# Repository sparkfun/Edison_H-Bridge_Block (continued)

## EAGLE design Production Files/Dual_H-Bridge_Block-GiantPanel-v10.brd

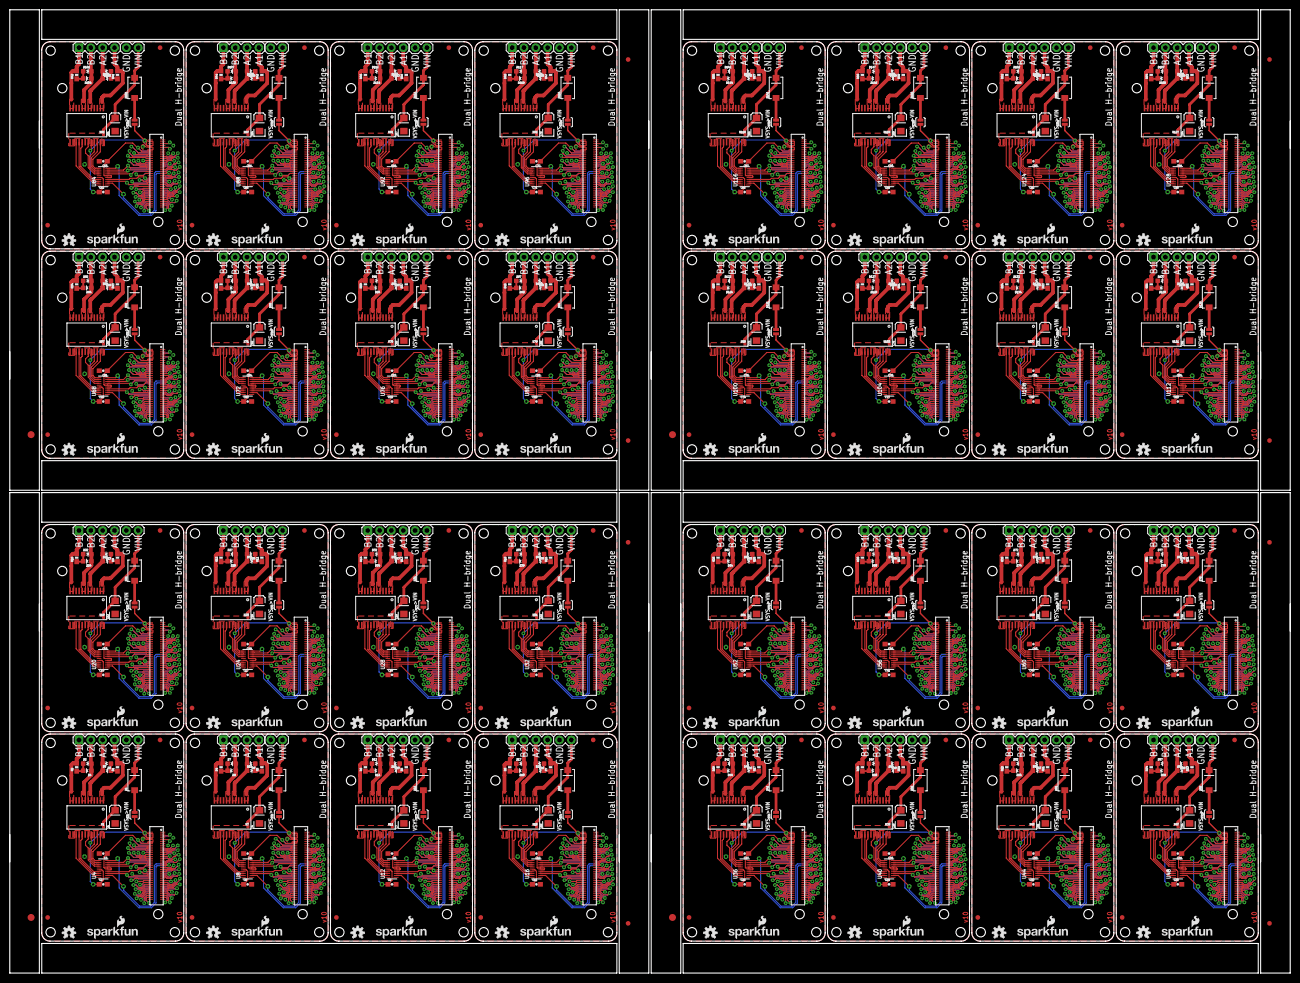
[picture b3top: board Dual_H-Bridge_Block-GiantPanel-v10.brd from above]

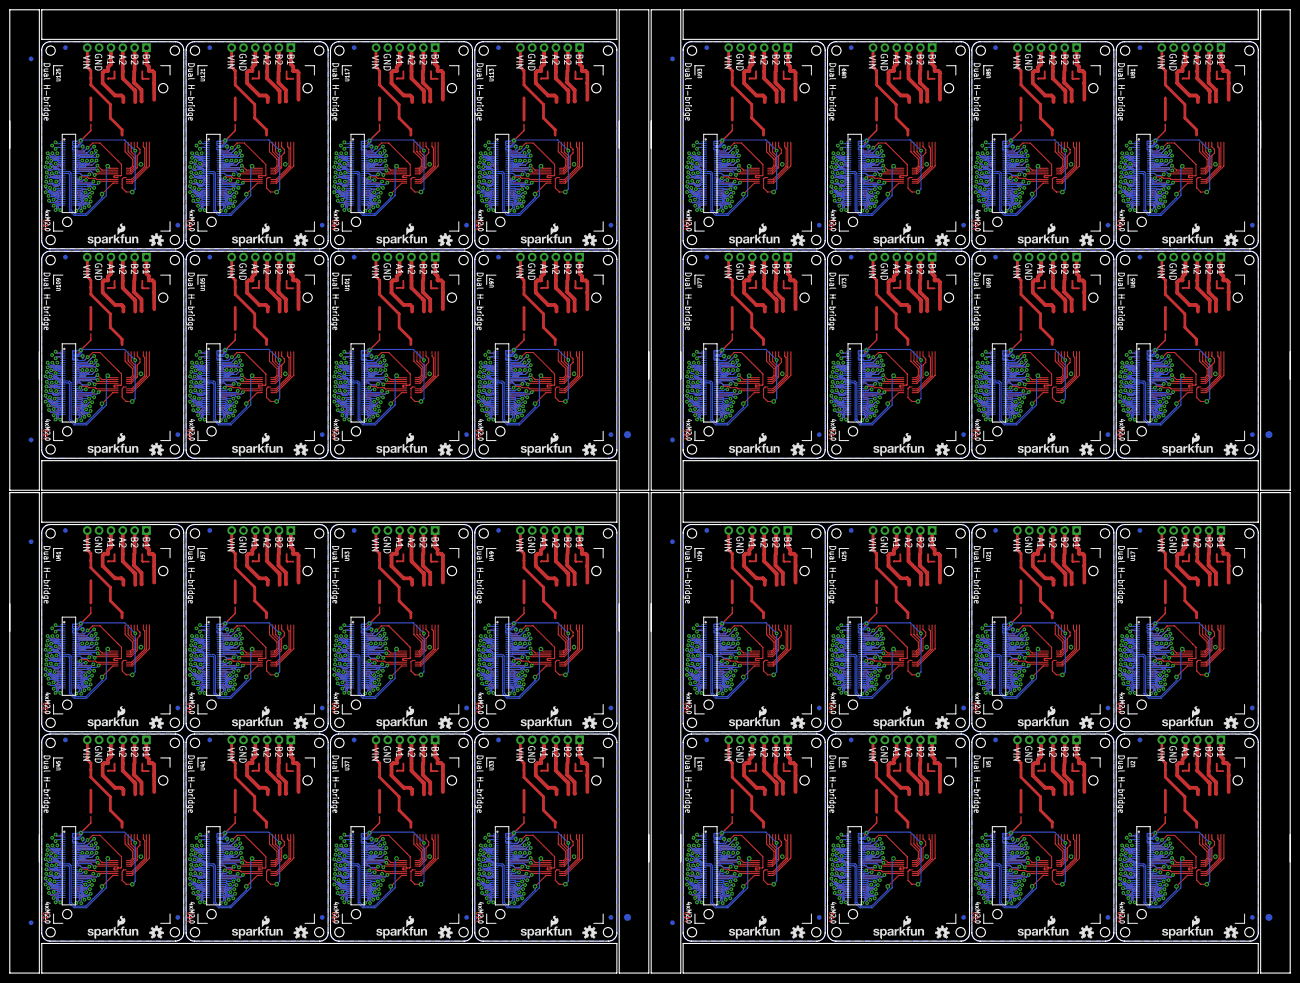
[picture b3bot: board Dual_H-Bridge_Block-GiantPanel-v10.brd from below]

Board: 2 copper layers, 274.8 x 206.8 mm, 824 parts (204 on the bottom side), 2336 nets.

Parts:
C1, C4, C7, C10, C13, C16, C19, C22, C25, C28, C31, C34, C37, C40, C43, C46, C49, C52, C55, C58, C61, C64, C67, C70, C73, C76, C79, C82, C85, C88, C91, C94: 10uF; EIA3216
C2, C3, C5, C6, C8, C9, C11, C12, C14, C15, C17, C18, C20, C21, C23, C24, C26, C27, C29, C30, C32, C33, C35, C36, C38, C39, C41, C42, C44, C45, C47, C48, C50, C51, C53, C54, C56, C57, C59, C60, C62, C63, C65, C66, C68, C69, C71, C72, C74, C75, C77, C78, C80, C81, C83, C84, C86, C87, C89, C90, C92, C93, C95, C96: 0.1uF; 0603-CAP
D1, D6, D11, D16, D21, D26, D31, D36, D41, D46, D51, D56, D61, D66, D71, D76, D81, D86, D91, D96, D101, D106, D111, D116, D121, D126, D131, D136, D141, D146, D151, D156: MBRA140; SMA-DIODE
D2, D3, D7, D8, D12, D13, D17, D18, D22, D23, D27, D28, D32, D33, D37, D38, D42, D43, D47, D48, D52, D53, D57, D58, D62, D63, D67, D68, D72, D73, D77, D78, D82, D83, D87, D88, D92, D93, D97, D98, D102, D103, D107, D108, D112, D113, D117, D118, D122, D123, D127, D128, D132, D133, D137, D138, D142, D143, D147, D148, D152, D153, D157, D158: GREEN; LED-0603
D4, D5, D9, D10, D14, D15, D19, D20, D24, D25, D29, D30, D34, D35, D39, D40, D44, D45, D49, D50, D54, D55, D59, D60, D64, D65, D69, D70, D74, D75, D79, D80, D84, D85, D89, D90, D94, D95, D99, D100, D104, D105, D109, D110, D114, D115, D119, D120, D124, D125, D129, D130, D134, D135, D139, D140, D144, D145, D149, D150, D154, D155, D159, D160: RED; LED-0603
E$1, E$2, E$11, E$12, E$17, E$18, E$23, E$24: FIDUCIAL-1.5X3
E$3, E$4, E$5, E$6, E$7, E$8, E$9, E$10, E$13, E$14, E$15, E$16, E$19, E$20, E$21, E$22: FIDUCIAL-1X2
FID1, FID2, FID3, FID4, FID5, FID6, FID7, FID8, FID9, FID10, FID11, FID12, FID13, FID14, FID15, FID16, FID17, FID18, FID19, FID20, FID21, FID22, FID23, FID24, FID25, FID26, FID27, FID28, FID29, FID30, FID31, FID32, FID33, FID34, FID35, FID36, FID37, FID38, FID39, FID40, FID41, FID42, FID43, FID44, FID45, FID46, FID47, FID48, FID49, FID50, FID51, FID52, FID53, FID54, FID55, FID56, FID57, FID58, FID59, FID60, FID61, FID62, FID63, FID64, FID65, FID66, FID67, FID68, FID69, FID70, FID71, FID72, FID73, FID74, FID75, FID76, FID77, FID78, FID79, FID80, FID81, FID82, FID83, FID84, FID85, FID86, FID87, FID88, FID89, FID90, FID91, FID92, FID93, FID94, FID95, FID96, FID97, FID98, FID99, FID100, FID101, FID102, FID103, FID104, FID105, FID106, FID107, FID108, FID109, FID110, FID111, FID112, FID113, FID114, FID115, FID116, FID117, FID118, FID119, FID120, FID121, FID122, FID123, FID124, FID125, FID126, FID127, FID128: FIDUCIAL1X2; FIDUCIAL-1X2
JP1, JP3, JP5, JP7, JP9, JP11, JP13, JP15, JP17, JP19, JP21, JP23, JP25, JP27, JP29, JP31, JP33, JP35, JP37, JP39, JP41, JP43, JP45, JP47, JP49, JP51, JP53, JP55, JP57, JP59, JP61, JP63: 1X04
JP2, JP4, JP6, JP8, JP10, JP12, JP14, JP16, JP18, JP20, JP22, JP24, JP26, JP28, JP30, JP32, JP34, JP36, JP38, JP40, JP42, JP44, JP46, JP48, JP50, JP52, JP54, JP56, JP58, JP60, JP62, JP64: M02PTH; 1X02
LOGO1, LOGO2, LOGO5, LOGO7, LOGO9, LOGO11, LOGO13, LOGO15, LOGO17, LOGO19, LOGO21, LOGO23, LOGO25, LOGO27, LOGO29, LOGO31, LOGO33, LOGO35, LOGO37, LOGO39, LOGO41, LOGO43, LOGO45, LOGO47, LOGO49, LOGO51, LOGO53, LOGO55, LOGO57, LOGO59, LOGO61, LOGO63, LOGO65, LOGO67, LOGO69, LOGO71, LOGO73, LOGO75, LOGO77, LOGO79, LOGO81, LOGO83, LOGO85, LOGO87, LOGO89, LOGO91, LOGO93, LOGO95, LOGO97, LOGO99, LOGO101, LOGO103, LOGO105, LOGO107, LOGO109, LOGO111, LOGO113, LOGO115, LOGO117, LOGO119, LOGO121, LOGO123, LOGO125, LOGO127: OSHW-LOGOS; OSHW-LOGO-S
LOGO3, LOGO4, LOGO6, LOGO8, LOGO10, LOGO12, LOGO14, LOGO16, LOGO18, LOGO20, LOGO22, LOGO24, LOGO26, LOGO28, LOGO30, LOGO32, LOGO34, LOGO36, LOGO38, LOGO40, LOGO42, LOGO44, LOGO46, LOGO48, LOGO50, LOGO52, LOGO54, LOGO56, LOGO58, LOGO60, LOGO62, LOGO64, LOGO66, LOGO68, LOGO70, LOGO72, LOGO74, LOGO76, LOGO78, LOGO80, LOGO82, LOGO84, LOGO86, LOGO88, LOGO90, LOGO92, LOGO94, LOGO96, LOGO98, LOGO100, LOGO102, LOGO104, LOGO106, LOGO108, LOGO110, LOGO112, LOGO114, LOGO116, LOGO118, LOGO120, LOGO122, LOGO124, LOGO126, LOGO128: SFE_LOGO_NAME_FLAME.1_INCH; SFE_LOGO_NAME_FLAME_.1
R1, R2, R3, R4, R5, R6, R7, R8, R9, R10, R11, R12, R13, R14, R15, R16, R17, R18, R19, R20, R21, R22, R23, R24, R25, R26, R27, R28, R29, R30, R31, R32, R33, R34, R35, R36, R37, R38, R39, R40, R41, R42, R43, R44, R45, R46, R47, R48, R49, R50, R51, R52, R53, R54, R55, R56, R57, R58, R59, R60, R61, R62, R63, R64: 680; 0603-RES
SJ1, SJ2, SJ3, SJ4, SJ5, SJ6, SJ7, SJ8, SJ9, SJ10, SJ11, SJ12, SJ13, SJ14, SJ15, SJ16, SJ17, SJ18, SJ19, SJ20, SJ21, SJ22, SJ23, SJ24, SJ25, SJ26, SJ27, SJ28, SJ29, SJ30, SJ31, SJ32: VSYS ENABLE; PAD-JUMPER-2-NO_YES_SILK
U1, U7, U11, U15, U19, U23, U27, U31, U35, U39, U43, U47, U51, U55, U59, U63, U67, U71, U75, U79, U83, U87, U91, U95, U99, U103, U107, U111, U115, U119, U123, U127: TB6612FNG; SSOP24
U2, U5, U9, U13, U17, U21, U25, U29, U33, U37, U41, U45, U49, U53, U57, U61, U65, U69, U73, U77, U81, U85, U89, U93, U97, U101, U105, U109, U113, U117, U121, U125: EDISON_CONNECTOR_FULLMOUNTING_HOLES; EDISON_DAUGHTER
U3, U6, U10, U14, U18, U22, U26, U30, U34, U38, U42, U46, U50, U54, U58, U62, U66, U70, U74, U78, U82, U86, U90, U94, U98, U102, U106, U110, U114, U118, U122, U126: EDISON_CONNECTOR_FULLHEADER; DF40C-70DP-0.4(51)
U4, U8, U12, U16, U20, U24, U28, U32, U36, U40, U44, U48, U52, U56, U60, U64, U68, U72, U76, U80, U84, U88, U92, U96, U100, U104, U108, U112, U116, U120, U124, U128: TXB0108; UFDFN-20

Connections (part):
1.8V: C3.1, U2.12, U3.12, U4.5, U4.6
1.8V1: C6.1, U5.12, U6.12, U8.5, U8.6
1.8V2: C9.1, U9.12, U10.12, U12.5, U12.6
1.8V3: C12.1, U13.12, U14.12, U16.5, U16.6
1.8V4: C15.1, U17.12, U18.12, U20.5, U20.6
1.8V5: C18.1, U21.12, U22.12, U24.5, U24.6
1.8V6: C21.1, U25.12, U26.12, U28.5, U28.6
1.8V7: C24.1, U29.12, U30.12, U32.5, U32.6
1.8V8: C27.1, U33.12, U34.12, U36.5, U36.6
1.8V9: C30.1, U37.12, U38.12, U40.5, U40.6
1.8V10: C33.1, U41.12, U42.12, U44.5, U44.6
1.8V11: C36.1, U45.12, U46.12, U48.5, U48.6
1.8V12: C39.1, U49.12, U50.12, U52.5, U52.6
1.8V13: C42.1, U53.12, U54.12, U56.5, U56.6
1.8V14: C45.1, U57.12, U58.12, U60.5, U60.6
1.8V15: C48.1, U61.12, U62.12, U64.5, U64.6
1.8V16: C51.1, U65.12, U66.12, U68.5, U68.6
1.8V17: C54.1, U69.12, U70.12, U72.5, U72.6
1.8V18: C57.1, U73.12, U74.12, U76.5, U76.6
1.8V19: C60.1, U77.12, U78.12, U80.5, U80.6
1.8V20: C63.1, U81.12, U82.12, U84.5, U84.6
1.8V21: C66.1, U85.12, U86.12, U88.5, U88.6
1.8V22: C69.1, U89.12, U90.12, U92.5, U92.6
1.8V23: C72.1, U93.12, U94.12, U96.5, U96.6
1.8V24: C75.1, U97.12, U98.12, U100.5, U100.6
1.8V25: C78.1, U101.12, U102.12, U104.5, U104.6
1.8V26: C81.1, U105.12, U106.12, U108.5, U108.6
1.8V27: C84.1, U109.12, U110.12, U112.5, U112.6
1.8V28: C87.1, U113.12, U114.12, U116.5, U116.6
1.8V29: C90.1, U117.12, U118.12, U120.5, U120.6
1.8V30: C93.1, U121.12, U122.12, U124.5, U124.6
1.8V31: C96.1, U125.12, U126.12, U128.5, U128.6
3.3V: U2.8, U2.10, U3.8, U3.10
3.3V1: U5.8, U5.10, U6.8, U6.10
3.3V2: U9.8, U9.10, U10.8, U10.10
3.3V3: U13.8, U13.10, U14.8, U14.10
3.3V4: U17.8, U17.10, U18.8, U18.10
3.3V5: U21.8, U21.10, U22.8, U22.10
3.3V6: U25.8, U25.10, U26.8, U26.10
3.3V7: U29.8, U29.10, U30.8, U30.10
3.3V8: U33.8, U33.10, U34.8, U34.10
3.3V9: U37.8, U37.10, U38.8, U38.10
3.3V10: U41.8, U41.10, U42.8, U42.10
3.3V11: U45.8, U45.10, U46.8, U46.10
3.3V12: U49.8, U49.10, U50.8, U50.10
3.3V13: U53.8, U53.10, U54.8, U54.10
3.3V14: U57.8, U57.10, U58.8, U58.10
3.3V15: U61.8, U61.10, U62.8, U62.10
3.3V16: U65.8, U65.10, U66.8, U66.10
3.3V17: U69.8, U69.10, U70.8, U70.10
3.3V18: U73.8, U73.10, U74.8, U74.10
3.3V19: U77.8, U77.10, U78.8, U78.10
3.3V20: U81.8, U81.10, U82.8, U82.10
3.3V21: U85.8, U85.10, U86.8, U86.10
3.3V22: U89.8, U89.10, U90.8, U90.10
3.3V23: U93.8, U93.10, U94.8, U94.10
3.3V24: U97.8, U97.10, U98.8, U98.10
3.3V25: U101.8, U101.10, U102.8, U102.10
3.3V26: U105.8, U105.10, U106.8, U106.10
3.3V27: U109.8, U109.10, U110.8, U110.10
3.3V28: U113.8, U113.10, U114.8, U114.10
3.3V29: U117.8, U117.10, U118.8, U118.10
3.3V30: U121.8, U121.10, U122.8, U122.10
3.3V31: U125.8, U125.10, U126.8, U126.10
A1: JP1.4, R1.2, U1.1, U1.2
A2: D3.C, D5.A, JP1.3, U1.5, U1.6
A3: D8.C, D10.A, JP3.3, U7.5, U7.6
A4: JP3.4, R3.2, U7.1, U7.2
A5: D13.C, D15.A, JP5.3, U11.5, U11.6
A6: JP5.4, R5.2, U11.1, U11.2
A7: D18.C, D20.A, JP7.3, U15.5, U15.6
A8: JP7.4, R7.2, U15.1, U15.2
A9: D23.C, D25.A, JP9.3, U19.5, U19.6
A10: JP9.4, R9.2, U19.1, U19.2
A11: D28.C, D30.A, JP11.3, U23.5, U23.6
A12: JP11.4, R11.2, U23.1, U23.2
A13: D33.C, D35.A, JP13.3, U27.5, U27.6
A14: JP13.4, R13.2, U27.1, U27.2
A15: D38.C, D40.A, JP15.3, U31.5, U31.6
A16: JP15.4, R15.2, U31.1, U31.2
A17: D43.C, D45.A, JP17.3, U35.5, U35.6
A18: JP17.4, R17.2, U35.1, U35.2
A19: D48.C, D50.A, JP19.3, U39.5, U39.6
A20: JP19.4, R19.2, U39.1, U39.2
A21: D53.C, D55.A, JP21.3, U43.5, U43.6
A22: JP21.4, R21.2, U43.1, U43.2
A23: D58.C, D60.A, JP23.3, U47.5, U47.6
A24: JP23.4, R23.2, U47.1, U47.2
A25: D63.C, D65.A, JP25.3, U51.5, U51.6
A26: JP25.4, R25.2, U51.1, U51.2
A27: D68.C, D70.A, JP27.3, U55.5, U55.6
A28: JP27.4, R27.2, U55.1, U55.2
A29: D73.C, D75.A, JP29.3, U59.5, U59.6
A30: JP29.4, R29.2, U59.1, U59.2
A31: D78.C, D80.A, JP31.3, U63.5, U63.6
A32: JP31.4, R31.2, U63.1, U63.2
A33: D83.C, D85.A, JP33.3, U67.5, U67.6
A34: JP33.4, R33.2, U67.1, U67.2
A35: D88.C, D90.A, JP35.3, U71.5, U71.6
A36: JP35.4, R35.2, U71.1, U71.2
A37: D93.C, D95.A, JP37.3, U75.5, U75.6
A38: JP37.4, R37.2, U75.1, U75.2
A39: D98.C, D100.A, JP39.3, U79.5, U79.6
A40: JP39.4, R39.2, U79.1, U79.2
A41: D103.C, D105.A, JP41.3, U83.5, U83.6
A42: JP41.4, R41.2, U83.1, U83.2
A43: D108.C, D110.A, JP43.3, U87.5, U87.6
A44: JP43.4, R43.2, U87.1, U87.2
A45: D113.C, D115.A, JP45.3, U91.5, U91.6
A46: JP45.4, R45.2, U91.1, U91.2
A47: D118.C, D120.A, JP47.3, U95.5, U95.6
A48: JP47.4, R47.2, U95.1, U95.2
A49: D123.C, D125.A, JP49.3, U99.5, U99.6
A50: JP49.4, R49.2, U99.1, U99.2
A51: D128.C, D130.A, JP51.3, U103.5, U103.6
A52: JP51.4, R51.2, U103.1, U103.2
A53: D133.C, D135.A, JP53.3, U107.5, U107.6
A54: JP53.4, R53.2, U107.1, U107.2
A55: D138.C, D140.A, JP55.3, U111.5, U111.6
A56: JP55.4, R55.2, U111.1, U111.2
A57: D143.C, D145.A, JP57.3, U115.5, U115.6
A58: JP57.4, R57.2, U115.1, U115.2
A59: D148.C, D150.A, JP59.3, U119.5, U119.6
A60: JP59.4, R59.2, U119.1, U119.2
A61: D153.C, D155.A, JP61.3, U123.5, U123.6
A62: JP61.4, R61.2, U123.1, U123.2
A63: D158.C, D160.A, JP63.3, U127.5, U127.6
A64: JP63.4, R63.2, U127.1, U127.2
B1: JP1.1, R2.2, U1.11, U1.12
B2: D2.C, D4.A, JP1.2, U1.7, U1.8
B3: JP3.1, R4.2, U7.11, U7.12
B4: D7.C, D9.A, JP3.2, U7.7, U7.8
B5: JP5.1, R6.2, U11.11, U11.12
B6: D12.C, D14.A, JP5.2, U11.7, U11.8
B7: JP7.1, R8.2, U15.11, U15.12
B8: D17.C, D19.A, JP7.2, U15.7, U15.8
B9: JP9.1, R10.2, U19.11, U19.12
B10: D22.C, D24.A, JP9.2, U19.7, U19.8
B11: JP11.1, R12.2, U23.11, U23.12
B12: D27.C, D29.A, JP11.2, U23.7, U23.8
B13: JP13.1, R14.2, U27.11, U27.12
B14: D32.C, D34.A, JP13.2, U27.7, U27.8
B15: JP15.1, R16.2, U31.11, U31.12
B16: D37.C, D39.A, JP15.2, U31.7, U31.8
B17: JP17.1, R18.2, U35.11, U35.12
B18: D42.C, D44.A, JP17.2, U35.7, U35.8
B19: JP19.1, R20.2, U39.11, U39.12
B20: D47.C, D49.A, JP19.2, U39.7, U39.8
B21: JP21.1, R22.2, U43.11, U43.12
B22: D52.C, D54.A, JP21.2, U43.7, U43.8
B23: JP23.1, R24.2, U47.11, U47.12
B24: D57.C, D59.A, JP23.2, U47.7, U47.8
B25: JP25.1, R26.2, U51.11, U51.12
B26: D62.C, D64.A, JP25.2, U51.7, U51.8
B27: JP27.1, R28.2, U55.11, U55.12
B28: D67.C, D69.A, JP27.2, U55.7, U55.8
B29: JP29.1, R30.2, U59.11, U59.12
B30: D72.C, D74.A, JP29.2, U59.7, U59.8
B31: JP31.1, R32.2, U63.11, U63.12
B32: D77.C, D79.A, JP31.2, U63.7, U63.8
B33: JP33.1, R34.2, U67.11, U67.12
B34: D82.C, D84.A, JP33.2, U67.7, U67.8
B35: JP35.1, R36.2, U71.11, U71.12
B36: D87.C, D89.A, JP35.2, U71.7, U71.8
B37: JP37.1, R38.2, U75.11, U75.12
B38: D92.C, D94.A, JP37.2, U75.7, U75.8
B39: JP39.1, R40.2, U79.11, U79.12
B40: D97.C, D99.A, JP39.2, U79.7, U79.8
B41: JP41.1, R42.2, U83.11, U83.12
B42: D102.C, D104.A, JP41.2, U83.7, U83.8
B43: JP43.1, R44.2, U87.11, U87.12
B44: D107.C, D109.A, JP43.2, U87.7, U87.8
B45: JP45.1, R46.2, U91.11, U91.12
B46: D112.C, D114.A, JP45.2, U91.7, U91.8
B47: JP47.1, R48.2, U95.11, U95.12
B48: D117.C, D119.A, JP47.2, U95.7, U95.8
B49: JP49.1, R50.2, U99.11, U99.12
B50: D122.C, D124.A, JP49.2, U99.7, U99.8
B51: JP51.1, R52.2, U103.11, U103.12
B52: D127.C, D129.A, JP51.2, U103.7, U103.8
B53: JP53.1, R54.2, U107.11, U107.12
B54: D132.C, D134.A, JP53.2, U107.7, U107.8
B55: JP55.1, R56.2, U111.11, U111.12
B56: D137.C, D139.A, JP55.2, U111.7, U111.8
B57: JP57.1, R58.2, U115.11, U115.12
B58: D142.C, D144.A, JP57.2, U115.7, U115.8
B59: JP59.1, R60.2, U119.11, U119.12
B60: D147.C, D149.A, JP59.2, U119.7, U119.8
B61: JP61.1, R62.2, U123.11, U123.12
B62: D152.C, D154.A, JP61.2, U123.7, U123.8
B63: JP63.1, R64.2, U127.11, U127.12
B64: D157.C, D159.A, JP63.2, U127.7, U127.8
DCIN: U2.14, U3.14
DCIN1: U5.14, U6.14
DCIN2: U9.14, U10.14
DCIN3: U13.14, U14.14
DCIN4: U17.14, U18.14
DCIN5: U21.14, U22.14
DCIN6: U25.14, U26.14
DCIN7: U29.14, U30.14
DCIN8: U33.14, U34.14
DCIN9: U37.14, U38.14
DCIN10: U41.14, U42.14
DCIN11: U45.14, U46.14
DCIN12: U49.14, U50.14
DCIN13: U53.14, U54.14
DCIN14: U57.14, U58.14
DCIN15: U61.14, U62.14
DCIN16: U65.14, U66.14
DCIN17: U69.14, U70.14
DCIN18: U73.14, U74.14
DCIN19: U77.14, U78.14
DCIN20: U81.14, U82.14
DCIN21: U85.14, U86.14
DCIN22: U89.14, U90.14
DCIN23: U93.14, U94.14
DCIN24: U97.14, U98.14
DCIN25: U101.14, U102.14
DCIN26: U105.14, U106.14
DCIN27: U109.14, U110.14
DCIN28: U113.14, U114.14
DCIN29: U117.14, U118.14
DCIN30: U121.14, U122.14
DCIN31: U125.14, U126.14
FAULT: U2.19, U3.19
FAULT1: U5.19, U6.19
FAULT2: U9.19, U10.19
FAULT3: U13.19, U14.19
FAULT4: U17.19, U18.19
FAULT5: U21.19, U22.19
FAULT6: U25.19, U26.19
FAULT7: U29.19, U30.19
FAULT8: U33.19, U34.19
FAULT9: U37.19, U38.19
FAULT10: U41.19, U42.19
FAULT11: U45.19, U46.19
FAULT12: U49.19, U50.19
FAULT13: U53.19, U54.19
FAULT14: U57.19, U58.19
FAULT15: U61.19, U62.19
FAULT16: U65.19, U66.19
FAULT17: U69.19, U70.19
FAULT18: U73.19, U74.19
FAULT19: U77.19, U78.19
FAULT20: U81.19, U82.19
FAULT21: U85.19, U86.19
FAULT22: U89.19, U90.19
FAULT23: U93.19, U94.19
FAULT24: U97.19, U98.19
FAULT25: U101.19, U102.19
FAULT26: U105.19, U106.19
FAULT27: U109.19, U110.19
FAULT28: U113.19, U114.19
FAULT29: U117.19, U118.19
FAULT30: U121.19, U122.19
FAULT31: U125.19, U126.19
FW_RCVR: U2.69, U3.69
FW_RCVR1: U5.69, U6.69
FW_RCVR2: U9.69, U10.69
FW_RCVR3: U13.69, U14.69
FW_RCVR4: U17.69, U18.69
FW_RCVR5: U21.69, U22.69
FW_RCVR6: U25.69, U26.69
FW_RCVR7: U29.69, U30.69
FW_RCVR8: U33.69, U34.69
FW_RCVR9: U37.69, U38.69
FW_RCVR10: U41.69, U42.69
FW_RCVR11: U45.69, U46.69
FW_RCVR12: U49.69, U50.69
FW_RCVR13: U53.69, U54.69
FW_RCVR14: U57.69, U58.69
FW_RCVR15: U61.69, U62.69
FW_RCVR16: U65.69, U66.69
FW_RCVR17: U69.69, U70.69
FW_RCVR18: U73.69, U74.69
FW_RCVR19: U77.69, U78.69
FW_RCVR20: U81.69, U82.69
FW_RCVR21: U85.69, U86.69
FW_RCVR22: U89.69, U90.69
FW_RCVR23: U93.69, U94.69
FW_RCVR24: U97.69, U98.69
FW_RCVR25: U101.69, U102.69
FW_RCVR26: U105.69, U106.69
FW_RCVR27: U109.69, U110.69
FW_RCVR28: U113.69, U114.69
FW_RCVR29: U117.69, U118.69
FW_RCVR30: U121.69, U122.69
FW_RCVR31: U125.69, U126.69
GND: C1.C, C2.2, C3.2, JP2.1, U1.3, U1.4, U1.9, U1.10, U1.18, U2.1, U2.5, U2.9, U2.11, U2.13, U2.15, U3.1, U3.5, U3.9, U3.11, U3.13, U3.15, U4.15
GND1: C4.C, C5.2, C6.2, JP4.1, U5.1, U5.5, U5.9, U5.11, U5.13, U5.15, U6.1, U6.5, U6.9, U6.11, U6.13, U6.15, U7.3, U7.4, U7.9, U7.10, U7.18, U8.15
GND2: C7.C, C8.2, C9.2, JP6.1, U9.1, U9.5, U9.9, U9.11, U9.13, U9.15, U10.1, U10.5, U10.9, U10.11, U10.13, U10.15, U11.3, U11.4, U11.9, U11.10, U11.18, U12.15
GND3: C10.C, C11.2, C12.2, JP8.1, U13.1, U13.5, U13.9, U13.11, U13.13, U13.15, U14.1, U14.5, U14.9, U14.11, U14.13, U14.15, U15.3, U15.4, U15.9, U15.10, U15.18, U16.15
GND4: C13.C, C14.2, C15.2, JP10.1, U17.1, U17.5, U17.9, U17.11, U17.13, U17.15, U18.1, U18.5, U18.9, U18.11, U18.13, U18.15, U19.3, U19.4, U19.9, U19.10, U19.18, U20.15
GND5: C16.C, C17.2, C18.2, JP12.1, U21.1, U21.5, U21.9, U21.11, U21.13, U21.15, U22.1, U22.5, U22.9, U22.11, U22.13, U22.15, U23.3, U23.4, U23.9, U23.10, U23.18, U24.15
GND6: C19.C, C20.2, C21.2, JP14.1, U25.1, U25.5, U25.9, U25.11, U25.13, U25.15, U26.1, U26.5, U26.9, U26.11, U26.13, U26.15, U27.3, U27.4, U27.9, U27.10, U27.18, U28.15
GND7: C22.C, C23.2, C24.2, JP16.1, U29.1, U29.5, U29.9, U29.11, U29.13, U29.15, U30.1, U30.5, U30.9, U30.11, U30.13, U30.15, U31.3, U31.4, U31.9, U31.10, U31.18, U32.15
GND8: C25.C, C26.2, C27.2, JP18.1, U33.1, U33.5, U33.9, U33.11, U33.13, U33.15, U34.1, U34.5, U34.9, U34.11, U34.13, U34.15, U35.3, U35.4, U35.9, U35.10, U35.18, U36.15
GND9: C28.C, C29.2, C30.2, JP20.1, U37.1, U37.5, U37.9, U37.11, U37.13, U37.15, U38.1, U38.5, U38.9, U38.11, U38.13, U38.15, U39.3, U39.4, U39.9, U39.10, U39.18, U40.15
GND10: C31.C, C32.2, C33.2, JP22.1, U41.1, U41.5, U41.9, U41.11, U41.13, U41.15, U42.1, U42.5, U42.9, U42.11, U42.13, U42.15, U43.3, U43.4, U43.9, U43.10, U43.18, U44.15
GND11: C34.C, C35.2, C36.2, JP24.1, U45.1, U45.5, U45.9, U45.11, U45.13, U45.15, U46.1, U46.5, U46.9, U46.11, U46.13, U46.15, U47.3, U47.4, U47.9, U47.10, U47.18, U48.15
GND12: C37.C, C38.2, C39.2, JP26.1, U49.1, U49.5, U49.9, U49.11, U49.13, U49.15, U50.1, U50.5, U50.9, U50.11, U50.13, U50.15, U51.3, U51.4, U51.9, U51.10, U51.18, U52.15
GND13: C40.C, C41.2, C42.2, JP28.1, U53.1, U53.5, U53.9, U53.11, U53.13, U53.15, U54.1, U54.5, U54.9, U54.11, U54.13, U54.15, U55.3, U55.4, U55.9, U55.10, U55.18, U56.15
GND14: C43.C, C44.2, C45.2, JP30.1, U57.1, U57.5, U57.9, U57.11, U57.13, U57.15, U58.1, U58.5, U58.9, U58.11, U58.13, U58.15, U59.3, U59.4, U59.9, U59.10, U59.18, U60.15
GND15: C46.C, C47.2, C48.2, JP32.1, U61.1, U61.5, U61.9, U61.11, U61.13, U61.15, U62.1, U62.5, U62.9, U62.11, U62.13, U62.15, U63.3, U63.4, U63.9, U63.10, U63.18, U64.15
GND16: C49.C, C50.2, C51.2, JP34.1, U65.1, U65.5, U65.9, U65.11, U65.13, U65.15, U66.1, U66.5, U66.9, U66.11, U66.13, U66.15, U67.3, U67.4, U67.9, U67.10, U67.18, U68.15
GND17: C52.C, C53.2, C54.2, JP36.1, U69.1, U69.5, U69.9, U69.11, U69.13, U69.15, U70.1, U70.5, U70.9, U70.11, U70.13, U70.15, U71.3, U71.4, U71.9, U71.10, U71.18, U72.15
GND18: C55.C, C56.2, C57.2, JP38.1, U73.1, U73.5, U73.9, U73.11, U73.13, U73.15, U74.1, U74.5, U74.9, U74.11, U74.13, U74.15, U75.3, U75.4, U75.9, U75.10, U75.18, U76.15
GND19: C58.C, C59.2, C60.2, JP40.1, U77.1, U77.5, U77.9, U77.11, U77.13, U77.15, U78.1, U78.5, U78.9, U78.11, U78.13, U78.15, U79.3, U79.4, U79.9, U79.10, U79.18, U80.15
GND20: C61.C, C62.2, C63.2, JP42.1, U81.1, U81.5, U81.9, U81.11, U81.13, U81.15, U82.1, U82.5, U82.9, U82.11, U82.13, U82.15, U83.3, U83.4, U83.9, U83.10, U83.18, U84.15
GND21: C64.C, C65.2, C66.2, JP44.1, U85.1, U85.5, U85.9, U85.11, U85.13, U85.15, U86.1, U86.5, U86.9, U86.11, U86.13, U86.15, U87.3, U87.4, U87.9, U87.10, U87.18, U88.15
GND22: C67.C, C68.2, C69.2, JP46.1, U89.1, U89.5, U89.9, U89.11, U89.13, U89.15, U90.1, U90.5, U90.9, U90.11, U90.13, U90.15, U91.3, U91.4, U91.9, U91.10, U91.18, U92.15
GND23: C70.C, C71.2, C72.2, JP48.1, U93.1, U93.5, U93.9, U93.11, U93.13, U93.15, U94.1, U94.5, U94.9, U94.11, U94.13, U94.15, U95.3, U95.4, U95.9, U95.10, U95.18, U96.15
GND24: C73.C, C74.2, C75.2, JP50.1, U97.1, U97.5, U97.9, U97.11, U97.13, U97.15, U98.1, U98.5, U98.9, U98.11, U98.13, U98.15, U99.3, U99.4, U99.9, U99.10, U99.18, U100.15
GND25: C76.C, C77.2, C78.2, JP52.1, U101.1, U101.5, U101.9, U101.11, U101.13, U101.15, U102.1, U102.5, U102.9, U102.11, U102.13, U102.15, U103.3, U103.4, U103.9, U103.10, U103.18, U104.15
GND26: C79.C, C80.2, C81.2, JP54.1, U105.1, U105.5, U105.9, U105.11, U105.13, U105.15, U106.1, U106.5, U106.9, U106.11, U106.13, U106.15, U107.3, U107.4, U107.9, U107.10, U107.18, U108.15
GND27: C82.C, C83.2, C84.2, JP56.1, U109.1, U109.5, U109.9, U109.11, U109.13, U109.15, U110.1, U110.5, U110.9, U110.11, U110.13, U110.15, U111.3, U111.4, U111.9, U111.10, U111.18, U112.15
GND28: C85.C, C86.2, C87.2, JP58.1, U113.1, U113.5, U113.9, U113.11, U113.13, U113.15, U114.1, U114.5, U114.9, U114.11, U114.13, U114.15, U115.3, U115.4, U115.9, U115.10, U115.18, U116.15
GND29: C88.C, C89.2, C90.2, JP60.1, U117.1, U117.5, U117.9, U117.11, U117.13, U117.15, U118.1, U118.5, U118.9, U118.11, U118.13, U118.15, U119.3, U119.4, U119.9, U119.10, U119.18, U120.15
GND30: C91.C, C92.2, C93.2, JP62.1, U121.1, U121.5, U121.9, U121.11, U121.13, U121.15, U122.1, U122.5, U122.9, U122.11, U122.13, U122.15, U123.3, U123.4, U123.9, U123.10, U123.18, U124.15
GND31: C94.C, C95.2, C96.2, JP64.1, U125.1, U125.5, U125.9, U125.11, U125.13, U125.15, U126.1, U126.5, U126.9, U126.11, U126.13, U126.15, U127.3, U127.4, U127.9, U127.10, U127.18, U128.15
GP1: U5.48, U6.48, U8.3
GP2: U5.42, U6.42, U8.4
GP3: U5.34, U6.34, U8.7
GP4: U5.32, U6.32, U8.8
GP5: U5.30, U6.30, U8.9
GP6: U5.28, U6.28
GP7: U5.26, U6.26
GP8: U5.25, U6.25
GP9: U5.24, U6.24
GP10: U9.48, U10.48, U12.3
GP11: U9.42, U10.42, U12.4
GP12: U9.34, U10.34, U12.7
GP12_PWM0: U2.35, U3.35, U4.10
GP12_PWM1: U5.35, U6.35, U8.10
GP12_PWM2: U9.35, U10.35, U12.10
GP12_PWM3: U13.35, U14.35, U16.10
GP12_PWM4: U17.35, U18.35, U20.10
GP12_PWM5: U21.35, U22.35, U24.10
GP12_PWM6: U25.35, U26.35, U28.10
GP12_PWM7: U29.35, U30.35, U32.10
GP12_PWM8: U33.35, U34.35, U36.10
GP12_PWM9: U37.35, U38.35, U40.10
GP12_PWM10: U41.35, U42.35, U44.10
GP12_PWM11: U45.35, U46.35, U48.10
GP12_PWM12: U49.35, U50.35, U52.10
GP12_PWM13: U53.35, U54.35, U56.10
GP12_PWM14: U57.35, U58.35, U60.10
GP12_PWM15: U61.35, U62.35, U64.10
GP12_PWM16: U65.35, U66.35, U68.10
GP12_PWM17: U69.35, U70.35, U72.10
GP12_PWM18: U73.35, U74.35, U76.10
GP12_PWM19: U77.35, U78.35, U80.10
GP12_PWM20: U81.35, U82.35, U84.10
GP12_PWM21: U85.35, U86.35, U88.10
GP12_PWM22: U89.35, U90.35, U92.10
GP12_PWM23: U93.35, U94.35, U96.10
GP12_PWM24: U97.35, U98.35, U100.10
GP12_PWM25: U101.35, U102.35, U104.10
GP12_PWM26: U105.35, U106.35, U108.10
GP12_PWM27: U109.35, U110.35, U112.10
GP12_PWM28: U113.35, U114.35, U116.10
GP12_PWM29: U117.35, U118.35, U120.10
GP12_PWM30: U121.35, U122.35, U124.10
GP12_PWM31: U125.35, U126.35, U128.10
GP13: U9.32, U10.32, U12.8
GP13_PWM1: U2.33, U3.33, U4.2
GP13_PWM2: U5.33, U6.33, U8.2
GP13_PWM3: U9.33, U10.33, U12.2
GP13_PWM4: U13.33, U14.33, U16.2
GP13_PWM5: U17.33, U18.33, U20.2
GP13_PWM6: U21.33, U22.33, U24.2
GP13_PWM7: U25.33, U26.33, U28.2
GP13_PWM8: U29.33, U30.33, U32.2
GP13_PWM9: U33.33, U34.33, U36.2
GP13_PWM10: U37.33, U38.33, U40.2
GP13_PWM11: U41.33, U42.33, U44.2
GP13_PWM12: U45.33, U46.33, U48.2
GP13_PWM13: U49.33, U50.33, U52.2
GP13_PWM14: U53.33, U54.33, U56.2
GP13_PWM15: U57.33, U58.33, U60.2
GP13_PWM16: U61.33, U62.33, U64.2
GP13_PWM17: U65.33, U66.33, U68.2
GP13_PWM18: U69.33, U70.33, U72.2
GP13_PWM19: U73.33, U74.33, U76.2
GP13_PWM20: U77.33, U78.33, U80.2
GP13_PWM21: U81.33, U82.33, U84.2
GP13_PWM22: U85.33, U86.33, U88.2
GP13_PWM23: U89.33, U90.33, U92.2
GP13_PWM24: U93.33, U94.33, U96.2
GP13_PWM25: U97.33, U98.33, U100.2
GP13_PWM26: U101.33, U102.33, U104.2
GP13_PWM27: U105.33, U106.33, U108.2
GP13_PWM28: U109.33, U110.33, U112.2
GP13_PWM29: U113.33, U114.33, U116.2
GP13_PWM30: U117.33, U118.33, U120.2
GP13_PWM31: U121.33, U122.33, U124.2
GP13_PWM32: U125.33, U126.33, U128.2
GP14: U2.48, U3.48, U4.3
GP15: U2.42, U3.42, U4.4
GP16: U9.30, U10.30, U12.9
GP17: U9.28, U10.28
GP18: U9.26, U10.26
GP19: U9.25, U10.25
GP19_I2C_1_SCL: U2.41, U3.41
GP19_I2C_1_SCL1: U5.41, U6.41
GP19_I2C_1_SCL2: U9.41, U10.41
GP19_I2C_1_SCL3: U13.41, U14.41
GP19_I2C_1_SCL4: U17.41, U18.41
GP19_I2C_1_SCL5: U21.41, U22.41
GP19_I2C_1_SCL6: U25.41, U26.41
GP19_I2C_1_SCL7: U29.41, U30.41
GP19_I2C_1_SCL8: U33.41, U34.41
GP19_I2C_1_SCL9: U37.41, U38.41
GP19_I2C_1_SCL10: U41.41, U42.41
GP19_I2C_1_SCL11: U45.41, U46.41
GP19_I2C_1_SCL12: U49.41, U50.41
GP19_I2C_1_SCL13: U53.41, U54.41
GP19_I2C_1_SCL14: U57.41, U58.41
GP19_I2C_1_SCL15: U61.41, U62.41
GP19_I2C_1_SCL16: U65.41, U66.41
GP19_I2C_1_SCL17: U69.41, U70.41
GP19_I2C_1_SCL18: U73.41, U74.41
GP19_I2C_1_SCL19: U77.41, U78.41
GP19_I2C_1_SCL20: U81.41, U82.41
GP19_I2C_1_SCL21: U85.41, U86.41
GP19_I2C_1_SCL22: U89.41, U90.41
GP19_I2C_1_SCL23: U93.41, U94.41
GP19_I2C_1_SCL24: U97.41, U98.41
GP19_I2C_1_SCL25: U101.41, U102.41
GP19_I2C_1_SCL26: U105.41, U106.41
GP19_I2C_1_SCL27: U109.41, U110.41
GP19_I2C_1_SCL28: U113.41, U114.41
GP19_I2C_1_SCL29: U117.41, U118.41
GP19_I2C_1_SCL30: U121.41, U122.41
GP19_I2C_1_SCL31: U125.41, U126.41
GP20: U9.24, U10.24
GP20_I2C_1_SDA: U2.43, U3.43
GP20_I2C_1_SDA1: U5.43, U6.43
GP20_I2C_1_SDA2: U9.43, U10.43
GP20_I2C_1_SDA3: U13.43, U14.43
GP20_I2C_1_SDA4: U17.43, U18.43
GP20_I2C_1_SDA5: U21.43, U22.43
GP20_I2C_1_SDA6: U25.43, U26.43
GP20_I2C_1_SDA7: U29.43, U30.43
GP20_I2C_1_SDA8: U33.43, U34.43
GP20_I2C_1_SDA9: U37.43, U38.43
GP20_I2C_1_SDA10: U41.43, U42.43
GP20_I2C_1_SDA11: U45.43, U46.43
GP20_I2C_1_SDA12: U49.43, U50.43
GP20_I2C_1_SDA13: U53.43, U54.43
GP20_I2C_1_SDA14: U57.43, U58.43
GP20_I2C_1_SDA15: U61.43, U62.43
GP20_I2C_1_SDA16: U65.43, U66.43
GP20_I2C_1_SDA17: U69.43, U70.43
GP20_I2C_1_SDA18: U73.43, U74.43
GP20_I2C_1_SDA19: U77.43, U78.43
GP20_I2C_1_SDA20: U81.43, U82.43
GP20_I2C_1_SDA21: U85.43, U86.43
GP20_I2C_1_SDA22: U89.43, U90.43
GP20_I2C_1_SDA23: U93.43, U94.43
GP20_I2C_1_SDA24: U97.43, U98.43
GP20_I2C_1_SDA25: U101.43, U102.43
GP20_I2C_1_SDA26: U105.43, U106.43
GP20_I2C_1_SDA27: U109.43, U110.43
GP20_I2C_1_SDA28: U113.43, U114.43
GP20_I2C_1_SDA29: U117.43, U118.43
GP20_I2C_1_SDA30: U121.43, U122.43
GP20_I2C_1_SDA31: U125.43, U126.43
GP21: U13.48, U14.48, U16.3
GP22: U13.42, U14.42, U16.4
GP23: U13.34, U14.34, U16.7
GP24: U13.32, U14.32, U16.8
GP25: U13.30, U14.30, U16.9
GP26: U13.28, U14.28
GP27: U13.26, U14.26
GP27_I2C_6_SCL: U2.45, U3.45
GP27_I2C_6_SCL1: U5.45, U6.45
GP27_I2C_6_SCL2: U9.45, U10.45
GP27_I2C_6_SCL3: U13.45, U14.45
GP27_I2C_6_SCL4: U17.45, U18.45
GP27_I2C_6_SCL5: U21.45, U22.45
GP27_I2C_6_SCL6: U25.45, U26.45
GP27_I2C_6_SCL7: U29.45, U30.45
GP27_I2C_6_SCL8: U33.45, U34.45
GP27_I2C_6_SCL9: U37.45, U38.45
GP27_I2C_6_SCL10: U41.45, U42.45
GP27_I2C_6_SCL11: U45.45, U46.45
GP27_I2C_6_SCL12: U49.45, U50.45
GP27_I2C_6_SCL13: U53.45, U54.45
GP27_I2C_6_SCL14: U57.45, U58.45
GP27_I2C_6_SCL15: U61.45, U62.45
GP27_I2C_6_SCL16: U65.45, U66.45
GP27_I2C_6_SCL17: U69.45, U70.45
GP27_I2C_6_SCL18: U73.45, U74.45
GP27_I2C_6_SCL19: U77.45, U78.45
GP27_I2C_6_SCL20: U81.45, U82.45
GP27_I2C_6_SCL21: U85.45, U86.45
GP27_I2C_6_SCL22: U89.45, U90.45
GP27_I2C_6_SCL23: U93.45, U94.45
GP27_I2C_6_SCL24: U97.45, U98.45
GP27_I2C_6_SCL25: U101.45, U102.45
GP27_I2C_6_SCL26: U105.45, U106.45
GP27_I2C_6_SCL27: U109.45, U110.45
GP27_I2C_6_SCL28: U113.45, U114.45
GP27_I2C_6_SCL29: U117.45, U118.45
GP27_I2C_6_SCL30: U121.45, U122.45
GP27_I2C_6_SCL31: U125.45, U126.45
GP28: U13.25, U14.25
GP28_I2C_6_SDA: U2.47, U3.47
GP28_I2C_6_SDA1: U5.47, U6.47
GP28_I2C_6_SDA2: U9.47, U10.47
GP28_I2C_6_SDA3: U13.47, U14.47
GP28_I2C_6_SDA4: U17.47, U18.47
GP28_I2C_6_SDA5: U21.47, U22.47
GP28_I2C_6_SDA6: U25.47, U26.47
GP28_I2C_6_SDA7: U29.47, U30.47
GP28_I2C_6_SDA8: U33.47, U34.47
GP28_I2C_6_SDA9: U37.47, U38.47
GP28_I2C_6_SDA10: U41.47, U42.47
GP28_I2C_6_SDA11: U45.47, U46.47
GP28_I2C_6_SDA12: U49.47, U50.47
GP28_I2C_6_SDA13: U53.47, U54.47
GP28_I2C_6_SDA14: U57.47, U58.47
GP28_I2C_6_SDA15: U61.47, U62.47
GP28_I2C_6_SDA16: U65.47, U66.47
GP28_I2C_6_SDA17: U69.47, U70.47
GP28_I2C_6_SDA18: U73.47, U74.47
GP28_I2C_6_SDA19: U77.47, U78.47
GP28_I2C_6_SDA20: U81.47, U82.47
GP28_I2C_6_SDA21: U85.47, U86.47
GP28_I2C_6_SDA22: U89.47, U90.47
GP28_I2C_6_SDA23: U93.47, U94.47
GP28_I2C_6_SDA24: U97.47, U98.47
GP28_I2C_6_SDA25: U101.47, U102.47
GP28_I2C_6_SDA26: U105.47, U106.47
GP28_I2C_6_SDA27: U109.47, U110.47
GP28_I2C_6_SDA28: U113.47, U114.47
GP28_I2C_6_SDA29: U117.47, U118.47
GP28_I2C_6_SDA30: U121.47, U122.47
GP28_I2C_6_SDA31: U125.47, U126.47
GP29: U13.24, U14.24
GP30: U17.48, U18.48, U20.3
GP31: U17.42, U18.42, U20.4
GP32: U17.34, U18.34, U20.7
GP33: U17.32, U18.32, U20.8
GP34: U17.30, U18.30, U20.9
GP35: U17.28, U18.28
GP36: U17.26, U18.26
GP37: U17.25, U18.25
GP38: U17.24, U18.24
GP39: U21.48, U22.48, U24.3
GP40: U21.42, U22.42, U24.4
GP40_I2S_2_CLK: U2.52, U3.52
GP40_I2S_2_CLK1: U5.52, U6.52
GP40_I2S_2_CLK2: U9.52, U10.52
GP40_I2S_2_CLK3: U13.52, U14.52
GP40_I2S_2_CLK4: U17.52, U18.52
GP40_I2S_2_CLK5: U21.52, U22.52
GP40_I2S_2_CLK6: U25.52, U26.52
GP40_I2S_2_CLK7: U29.52, U30.52
GP40_I2S_2_CLK8: U33.52, U34.52
GP40_I2S_2_CLK9: U37.52, U38.52
GP40_I2S_2_CLK10: U41.52, U42.52
GP40_I2S_2_CLK11: U45.52, U46.52
GP40_I2S_2_CLK12: U49.52, U50.52
GP40_I2S_2_CLK13: U53.52, U54.52
GP40_I2S_2_CLK14: U57.52, U58.52
GP40_I2S_2_CLK15: U61.52, U62.52
GP40_I2S_2_CLK16: U65.52, U66.52
GP40_I2S_2_CLK17: U69.52, U70.52
GP40_I2S_2_CLK18: U73.52, U74.52
GP40_I2S_2_CLK19: U77.52, U78.52
GP40_I2S_2_CLK20: U81.52, U82.52
GP40_I2S_2_CLK21: U85.52, U86.52
GP40_I2S_2_CLK22: U89.52, U90.52
GP40_I2S_2_CLK23: U93.52, U94.52
GP40_I2S_2_CLK24: U97.52, U98.52
GP40_I2S_2_CLK25: U101.52, U102.52
GP40_I2S_2_CLK26: U105.52, U106.52
GP40_I2S_2_CLK27: U109.52, U110.52
GP40_I2S_2_CLK28: U113.52, U114.52
GP40_I2S_2_CLK29: U117.52, U118.52
GP40_I2S_2_CLK30: U121.52, U122.52
GP40_I2S_2_CLK31: U125.52, U126.52
GP41: U21.34, U22.34, U24.7
GP41_I2S_2_FS: U2.54, U3.54
GP41_I2S_2_FS1: U5.54, U6.54
GP41_I2S_2_FS2: U9.54, U10.54
GP41_I2S_2_FS3: U13.54, U14.54
GP41_I2S_2_FS4: U17.54, U18.54
GP41_I2S_2_FS5: U21.54, U22.54
GP41_I2S_2_FS6: U25.54, U26.54
GP41_I2S_2_FS7: U29.54, U30.54
GP41_I2S_2_FS8: U33.54, U34.54
GP41_I2S_2_FS9: U37.54, U38.54
GP41_I2S_2_FS10: U41.54, U42.54
GP41_I2S_2_FS11: U45.54, U46.54
GP41_I2S_2_FS12: U49.54, U50.54
GP41_I2S_2_FS13: U53.54, U54.54
GP41_I2S_2_FS14: U57.54, U58.54
GP41_I2S_2_FS15: U61.54, U62.54
GP41_I2S_2_FS16: U65.54, U66.54
GP41_I2S_2_FS17: U69.54, U70.54
GP41_I2S_2_FS18: U73.54, U74.54
GP41_I2S_2_FS19: U77.54, U78.54
GP41_I2S_2_FS20: U81.54, U82.54
GP41_I2S_2_FS21: U85.54, U86.54
GP41_I2S_2_FS22: U89.54, U90.54
GP41_I2S_2_FS23: U93.54, U94.54
GP41_I2S_2_FS24: U97.54, U98.54
GP41_I2S_2_FS25: U101.54, U102.54
GP41_I2S_2_FS26: U105.54, U106.54
GP41_I2S_2_FS27: U109.54, U110.54
GP41_I2S_2_FS28: U113.54, U114.54
GP41_I2S_2_FS29: U117.54, U118.54
GP41_I2S_2_FS30: U121.54, U122.54
GP41_I2S_2_FS31: U125.54, U126.54
GP42: U21.32, U22.32, U24.8
GP42_I2S_2_RXD: U2.50, U3.50
GP42_I2S_2_RXD1: U5.50, U6.50
GP42_I2S_2_RXD2: U9.50, U10.50
GP42_I2S_2_RXD3: U13.50, U14.50
GP42_I2S_2_RXD4: U17.50, U18.50
GP42_I2S_2_RXD5: U21.50, U22.50
GP42_I2S_2_RXD6: U25.50, U26.50
GP42_I2S_2_RXD7: U29.50, U30.50
GP42_I2S_2_RXD8: U33.50, U34.50
GP42_I2S_2_RXD9: U37.50, U38.50
GP42_I2S_2_RXD10: U41.50, U42.50
GP42_I2S_2_RXD11: U45.50, U46.50
GP42_I2S_2_RXD12: U49.50, U50.50
GP42_I2S_2_RXD13: U53.50, U54.50
GP42_I2S_2_RXD14: U57.50, U58.50
GP42_I2S_2_RXD15: U61.50, U62.50
GP42_I2S_2_RXD16: U65.50, U66.50
GP42_I2S_2_RXD17: U69.50, U70.50
GP42_I2S_2_RXD18: U73.50, U74.50
GP42_I2S_2_RXD19: U77.50, U78.50
GP42_I2S_2_RXD20: U81.50, U82.50
GP42_I2S_2_RXD21: U85.50, U86.50
GP42_I2S_2_RXD22: U89.50, U90.50
GP42_I2S_2_RXD23: U93.50, U94.50
GP42_I2S_2_RXD24: U97.50, U98.50
GP42_I2S_2_RXD25: U101.50, U102.50
GP42_I2S_2_RXD26: U105.50, U106.50
GP42_I2S_2_RXD27: U109.50, U110.50
GP42_I2S_2_RXD28: U113.50, U114.50
GP42_I2S_2_RXD29: U117.50, U118.50
GP42_I2S_2_RXD30: U121.50, U122.50
GP42_I2S_2_RXD31: U125.50, U126.50
GP43: U21.30, U22.30, U24.9
GP43_I2S_2_TXD: U2.56, U3.56
GP43_I2S_2_TXD1: U5.56, U6.56
GP43_I2S_2_TXD2: U9.56, U10.56
GP43_I2S_2_TXD3: U13.56, U14.56
GP43_I2S_2_TXD4: U17.56, U18.56
GP43_I2S_2_TXD5: U21.56, U22.56
GP43_I2S_2_TXD6: U25.56, U26.56
GP43_I2S_2_TXD7: U29.56, U30.56
GP43_I2S_2_TXD8: U33.56, U34.56
GP43_I2S_2_TXD9: U37.56, U38.56
GP43_I2S_2_TXD10: U41.56, U42.56
GP43_I2S_2_TXD11: U45.56, U46.56
GP43_I2S_2_TXD12: U49.56, U50.56
GP43_I2S_2_TXD13: U53.56, U54.56
GP43_I2S_2_TXD14: U57.56, U58.56
GP43_I2S_2_TXD15: U61.56, U62.56
GP43_I2S_2_TXD16: U65.56, U66.56
GP43_I2S_2_TXD17: U69.56, U70.56
GP43_I2S_2_TXD18: U73.56, U74.56
GP43_I2S_2_TXD19: U77.56, U78.56
GP43_I2S_2_TXD20: U81.56, U82.56
GP43_I2S_2_TXD21: U85.56, U86.56
GP43_I2S_2_TXD22: U89.56, U90.56
GP43_I2S_2_TXD23: U93.56, U94.56
GP43_I2S_2_TXD24: U97.56, U98.56
GP43_I2S_2_TXD25: U101.56, U102.56
GP43_I2S_2_TXD26: U105.56, U106.56
GP43_I2S_2_TXD27: U109.56, U110.56
GP43_I2S_2_TXD28: U113.56, U114.56
GP43_I2S_2_TXD29: U117.56, U118.56
GP43_I2S_2_TXD30: U121.56, U122.56
GP43_I2S_2_TXD31: U125.56, U126.56
GP44: U2.24, U3.24
GP45: U2.26, U3.26
GP46: U2.28, U3.28
GP47: U2.30, U3.30, U4.9
GP48: U2.32, U3.32, U4.8
GP49: U2.34, U3.34, U4.7
GP50: U21.28, U22.28
GP51: U21.26, U22.26
GP52: U21.25, U22.25
GP53: U21.24, U22.24
GP54: U25.48, U26.48, U28.3
GP55: U25.42, U26.42, U28.4
GP56: U25.34, U26.34, U28.7
GP57: U25.32, U26.32, U28.8
GP58: U25.30, U26.30, U28.9
GP59: U25.28, U26.28
GP60: U25.26, U26.26
GP61: U25.25, U26.25
GP62: U25.24, U26.24
GP63: U29.48, U30.48, U32.3
GP64: U29.42, U30.42, U32.4
GP65: U29.34, U30.34, U32.7
GP66: U29.32, U30.32, U32.8
GP67: U29.30, U30.30, U32.9
GP68: U29.28, U30.28
GP69: U29.26, U30.26
GP70: U29.25, U30.25
GP71: U29.24, U30.24
GP72: U33.48, U34.48, U36.3
GP73: U33.42, U34.42, U36.4
GP74: U33.34, U34.34, U36.7
GP75: U33.32, U34.32, U36.8
GP76: U33.30, U34.30, U36.9
GP77: U33.28, U34.28
GP77_SD_0_CD#: U2.60, U3.60
GP77_SD_0_CD#1: U5.60, U6.60
GP77_SD_0_CD#2: U9.60, U10.60
GP77_SD_0_CD#3: U13.60, U14.60
GP77_SD_0_CD#4: U17.60, U18.60
GP77_SD_0_CD#5: U21.60, U22.60
GP77_SD_0_CD#6: U25.60, U26.60
GP77_SD_0_CD#7: U29.60, U30.60
GP77_SD_0_CD#8: U33.60, U34.60
GP77_SD_0_CD#9: U37.60, U38.60
GP77_SD_0_CD#10: U41.60, U42.60
GP77_SD_0_CD#11: U45.60, U46.60
GP77_SD_0_CD#12: U49.60, U50.60
GP77_SD_0_CD#13: U53.60, U54.60
GP77_SD_0_CD#14: U57.60, U58.60
GP77_SD_0_CD#15: U61.60, U62.60
GP77_SD_0_CD#16: U65.60, U66.60
GP77_SD_0_CD#17: U69.60, U70.60
GP77_SD_0_CD#18: U73.60, U74.60
GP77_SD_0_CD#19: U77.60, U78.60
GP77_SD_0_CD#20: U81.60, U82.60
GP77_SD_0_CD#21: U85.60, U86.60
GP77_SD_0_CD#22: U89.60, U90.60
GP77_SD_0_CD#23: U93.60, U94.60
GP77_SD_0_CD#24: U97.60, U98.60
GP77_SD_0_CD#25: U101.60, U102.60
GP77_SD_0_CD#26: U105.60, U106.60
GP77_SD_0_CD#27: U109.60, U110.60
GP77_SD_0_CD#28: U113.60, U114.60
GP77_SD_0_CD#29: U117.60, U118.60
GP77_SD_0_CD#30: U121.60, U122.60
GP77_SD_0_CD#31: U125.60, U126.60
GP78: U33.26, U34.26
GP78_SD_0_CLK: U2.58, U3.58
GP78_SD_0_CLK1: U5.58, U6.58
GP78_SD_0_CLK2: U9.58, U10.58
GP78_SD_0_CLK3: U13.58, U14.58
GP78_SD_0_CLK4: U17.58, U18.58
GP78_SD_0_CLK5: U21.58, U22.58
GP78_SD_0_CLK6: U25.58, U26.58
GP78_SD_0_CLK7: U29.58, U30.58
GP78_SD_0_CLK8: U33.58, U34.58
GP78_SD_0_CLK9: U37.58, U38.58
GP78_SD_0_CLK10: U41.58, U42.58
GP78_SD_0_CLK11: U45.58, U46.58
GP78_SD_0_CLK12: U49.58, U50.58
GP78_SD_0_CLK13: U53.58, U54.58
GP78_SD_0_CLK14: U57.58, U58.58
GP78_SD_0_CLK15: U61.58, U62.58
GP78_SD_0_CLK16: U65.58, U66.58
GP78_SD_0_CLK17: U69.58, U70.58
GP78_SD_0_CLK18: U73.58, U74.58
GP78_SD_0_CLK19: U77.58, U78.58
GP78_SD_0_CLK20: U81.58, U82.58
GP78_SD_0_CLK21: U85.58, U86.58
GP78_SD_0_CLK22: U89.58, U90.58
GP78_SD_0_CLK23: U93.58, U94.58
GP78_SD_0_CLK24: U97.58, U98.58
GP78_SD_0_CLK25: U101.58, U102.58
GP78_SD_0_CLK26: U105.58, U106.58
GP78_SD_0_CLK27: U109.58, U110.58
GP78_SD_0_CLK28: U113.58, U114.58
GP78_SD_0_CLK29: U117.58, U118.58
GP78_SD_0_CLK30: U121.58, U122.58
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
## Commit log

2014-08-12 initial commit with completed layout, Ready for review
2014-08-12 removed Edzzanine from name
2014-08-14 fixed OE high
2014-08-28 Updated Readme with small description
2014-09-22 Added LED's for motor direction Added Diode Jumper circuit to enable VSYS to power VIN Corrected Name and location Removed extra dimensions and cleaned up drawing Added DCIN pin and completed circuit.
2014-09-22 killed .epf
2014-09-22 corrected labels
2014-09-23 changed names of files
2014-09-25 file cleanup
2014-10-17 corrected package footprint to remove bridging.
2014-10-17 fixed text to vector
2014-10-17 fixed pours
2014-10-17 fixed level shifter pad jumper
2014-10-17 Changed Logic to vsys from vin
2014-10-17 finishing routing and cleaning up pads
2014-10-17 Ready for reds. Change LED resistors to 680 ohm Thicken traces of drive Touch up schematic No known to-do items
2014-10-22 created v10 panels
